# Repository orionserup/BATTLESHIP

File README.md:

# BATTLESHIP
A small battleship game built on a custom PCB using cheap chinese parts

Runs using a series of Shift registers running a custom game library, game library is based
on the popular shift register library

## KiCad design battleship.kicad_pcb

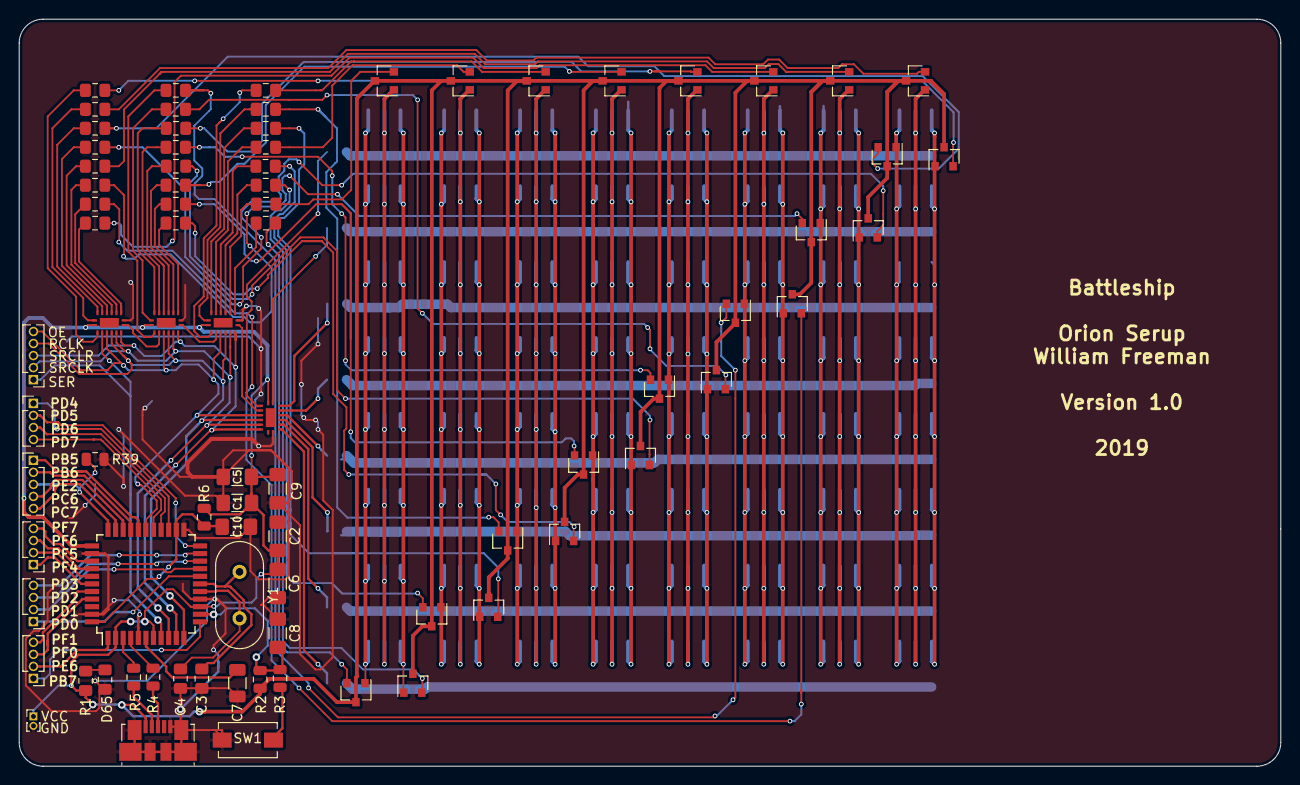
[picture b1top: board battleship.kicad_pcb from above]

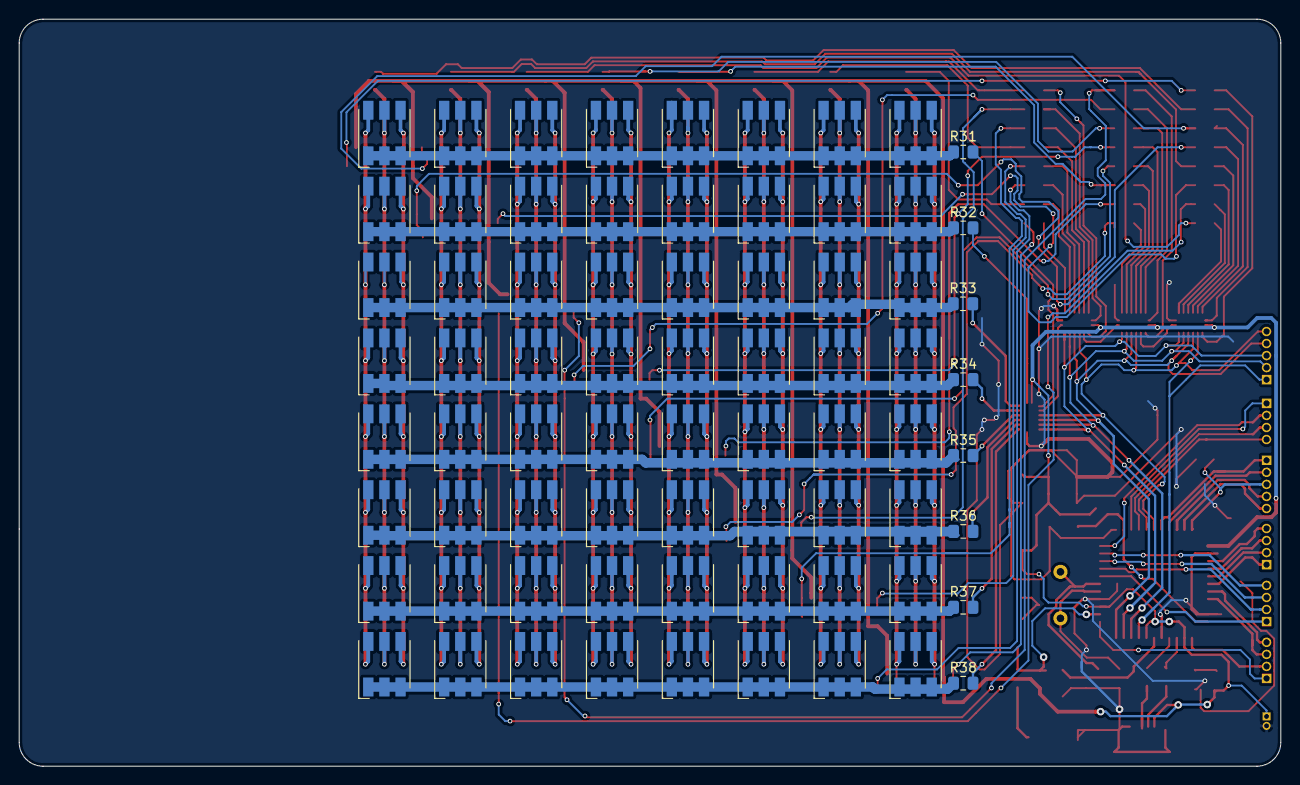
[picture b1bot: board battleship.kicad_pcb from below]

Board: 2 copper layers, 133.0 x 78.8 mm, 153 parts (72 on the bottom side), 130 nets.

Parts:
C1, C2, C5, C6, C9: 10UF; R_1206_3216Metric_Pad1.42x1.75mm_HandSolder
C3, C4: 22pf; C_0805_2012Metric_Pad1.15x1.40mm_HandSolder
C7: 1uF; R_1206_3216Metric
C8: 100nf; C_1206_3216Metric_Pad1.42x1.75mm_HandSolder
C10: 10uF; R_1206_3216Metric_Pad1.42x1.75mm_HandSolder
D1, D2, D3, D4, D5, D6, D7, D8, D9, D10, D11, D12, D13, D14, D15, D16, D17, D18, D19, D20, D21, D22, D23, D24, D25, D26, D27, D28, D29, D30, D31, D32, D33, D34, D35, D36, D37, D38, D39, D40, D41, D42, D43, D44, D45, D46, D47, D48, D49, D50, D51, D52, D53, D54, D55, D56, D57, D58, D59, D60, D61, D62, D63, D64: ASMT-YTC2-0AA02; LED_RGB_5050-6
D65: LED; R_0805_2012Metric_Pad1.15x1.40mm_HandSolder
J1: USB_B_Micro; USB_Micro-B_Molex_47346-0001
J2, J3, J4, J7: Conn_01x04; PinHeader_1x04_P1.27mm_Vertical
J5, J6: Conn_01x05; PinHeader_1x05_P1.27mm_Vertical
J8: Conn_01x02; PinHeader_1x02_P1.00mm_Vertical
Q1, Q2, Q3, Q4, Q5, Q6, Q7, Q8, Q9, Q10, Q11, Q12, Q13, Q14, Q15, Q16, Q17, Q18, Q19, Q20, Q21, Q22, Q23, Q24: 2N2219; SOT-23
R1: 1k; R_0805_2012Metric_Pad1.15x1.40mm_HandSolder
R2: 4.7k; R_0805_2012Metric
R3: 330; R_0805_2012Metric
R4, R5: 22; R_0805_2012Metric
R6: 1M; R_0805_2012Metric
R7, R8, R9, R10, R11, R12, R13, R14, R15, R16, R17, R18, R19, R20, R21, R22, R23, R24, R25, R26, R27, R28, R29, R30: 4.7K; R_0805_2012Metric_Pad1.15x1.40mm_HandSolder
R31, R32, R33, R34, R35, R36, R37, R38: 1K; R_0805_2012Metric_Pad1.15x1.40mm_HandSolder
R39: 1k; R_0805_2012Metric
SW1: SW_DPST_x2; SW_SPST_EVQPE1
U1: ATmega32U4RC-AU; TQFP-44_10x10mm_P0.8mm
U2, U3, U4, U5: 74HC595; dvqfn
Y1: 16MHz; Crystal_HC18-U_Vertical

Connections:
1: D1.6, D2.6, D3.6, D4.6, D5.6, D6.6, D7.6, D8.6, Q1.1
2: D1.5, D2.5, D3.5, D4.5, D5.5, D6.5, D7.5, D8.5, Q3.1
3: D1.4, D2.4, D3.4, D4.4, D5.4, D6.4, D7.4, D8.4, Q5.1
4: D9.6, D10.6, D11.6, D12.6, D13.6, D14.6, D15.6, D16.6, Q7.1
5: D9.5, D10.5, D11.5, D12.5, D13.5, D14.5, D15.5, D16.5, Q9.1
6: D9.4, D10.4, D11.4, D12.4, D13.4, D14.4, D15.4, D16.4, Q11.1
7: D17.6, D18.6, D19.6, D20.6, D21.6, D22.6, D23.6, D24.6, Q13.1
8: D17.5, D18.5, D19.5, D20.5, D21.5, D22.5, D23.5, D24.5, Q15.1
9: D17.4, D18.4, D19.4, D20.4, D21.4, D22.4, D23.4, D24.4, Q17.1
10: D25.6, D26.6, D27.6, D28.6, D29.6, D30.6, D31.6, D32.6, Q19.1
11: D25.5, D26.5, D27.5, D28.5, D29.5, D30.5, D31.5, D32.5, Q21.1
12: D25.4, D26.4, D27.4, D28.4, D29.4, D30.4, D31.4, D32.4, Q23.1
13: D33.6, D34.6, D35.6, D36.6, D37.6, D38.6, D39.6, D40.6, Q2.1
14: D33.5, D34.5, D35.5, D36.5, D37.5, D38.5, D39.5, D40.5, Q4.1
15: D33.4, D34.4, D35.4, D36.4, D37.4, D38.4, D39.4, D40.4, Q6.1
16: D41.6, D42.6, D43.6, D44.6, D45.6, D46.6, D47.6, D48.6, Q8.1
17: D41.5, D42.5, D43.5, D44.5, D45.5, D46.5, D47.5, D48.5, Q10.1
18: D41.4, D42.4, D43.4, D44.4, D45.4, D46.4, D47.4, D48.4, Q12.1
19: D49.6, D50.6, D51.6, D52.6, D53.6, D54.6, D55.6, D56.6, Q14.1
20: D49.5, D50.5, D51.5, D52.5, D53.5, D54.5, D55.5, D56.5, Q16.1
21: D49.4, D50.4, D51.4, D52.4, D53.4, D54.4, D55.4, D56.4, Q18.1
22: D57.6, D58.6, D59.6, D60.6, D61.6, D62.6, D63.6, D64.6, Q20.1
23: D57.5, D58.5, D59.5, D60.5, D61.5, D62.5, D63.5, D64.5, Q22.1
24: D57.4, D58.4, D59.4, D60.4, D61.4, D62.4, D63.4, D64.4, Q24.1
25: D1.1, D1.2, D1.3, D9.1, D9.2, D9.3, D17.1, D17.2, D17.3, D25.1, D25.2, D25.3, D33.1, D33.2, D33.3, D41.1, D41.2, D41.3, D49.1, D49.2, D49.3, D57.1, D57.2, D57.3, R31.1
26: D2.1, D2.2, D2.3, D10.1, D10.2, D10.3, D18.1, D18.2, D18.3, D26.1, D26.2, D26.3, D34.1, D34.2, D34.3, D42.1, D42.2, D42.3, D50.1, D50.2, D50.3, D58.1, D58.2, D58.3, R32.1
27: D3.1, D3.2, D3.3, D11.1, D11.2, D11.3, D19.1, D19.2, D19.3, D27.1, D27.2, D27.3, D35.1, D35.2, D35.3, D43.1, D43.2, D43.3, D51.1, D51.2, D51.3, D59.1, D59.2, D59.3, R33.1
28: D4.1, D4.2, D4.3, D12.1, D12.2, D12.3, D20.1, D20.2, D20.3, D28.1, D28.2, D28.3, D36.1, D36.2, D36.3, D44.1, D44.2, D44.3, D52.1, D52.2, D52.3, D60.1, D60.2, D60.3, R34.1
29: D5.1, D5.2, D5.3, D13.1, D13.2, D13.3, D21.1, D21.2, D21.3, D29.1, D29.2, D29.3, D37.1, D37.2, D37.3, D45.1, D45.2, D45.3, D53.1, D53.2, D53.3, D61.1, D61.2, D61.3, R35.1
30: D6.1, D6.2, D6.3, D14.1, D14.2, D14.3, D22.1, D22.2, D22.3, D30.1, D30.2, D30.3, D38.1, D38.2, D38.3, D46.1, D46.2, D46.3, D54.1, D54.2, D54.3, D62.1, D62.2, D62.3, R36.1
31: D7.1, D7.2, D7.3, D15.1, D15.2, D15.3, D23.1, D23.2, D23.3, D31.1, D31.2, D31.3, D39.1, D39.2, D39.3, D47.1, D47.2, D47.3, D55.1, D55.2, D55.3, D63.1, D63.2, D63.3, R37.1
32: D8.1, D8.2, D8.3, D16.1, D16.2, D16.3, D24.1, D24.2, D24.3, D32.1, D32.2, D32.3, D40.1, D40.2, D40.3, D48.1, D48.2, D48.3, D56.1, D56.2, D56.3, D64.1, D64.2, D64.3, R38.1
/PB5: J6.1, U1.29
/RESET: C8.2, R2.2, R3.1, U1.13
/SER: J5.1, U1.8, U2.14
/pb6: J6.2, U1.30
/pb7: J7.1, U1.12
/pc6: J6.4, U1.31
/pc7: J6.5, U1.32
/pd0: J2.1, U1.18
/pd1: J2.2, U1.19
/pd2: J2.3, U1.20
/pd3: J2.4, U1.21
/pd4: J3.1, U1.25
/pd5: J3.2, U1.22
/pd6: J3.3, U1.26
/pd7: J3.4, U1.27
/pe6: J7.2, U1.1
/pf0: J7.3, U1.41
/pf1: J7.4, U1.40
/pf4: J4.1, U1.39
/pf5: J4.2, U1.38
/pf6: J4.3, U1.37
/pf7: J4.4, U1.36
A1: Q1.2, R7.1
A2: Q3.2, R8.1
A3: Q5.2, R9.1
A4: Q7.2, R10.1
A5: Q9.2, R11.1
A6: Q11.2, R12.1
A7: Q13.2, R13.1
A8: Q15.2, R14.1
A9: Q17.2, R15.1
A10: Q19.2, R16.1
A11: Q21.2, R17.1
A12: Q23.2, R18.1
A13: Q2.2, R19.1
A14: Q4.2, R20.1
A15: Q6.2, R21.1
A16: Q8.2, R22.1
A17: Q10.2, R23.1
A18: Q12.2, R24.1
A19: Q14.2, R25.1
A20: Q16.2, R26.1
A21: Q18.2, R27.1
A22: Q20.2, R28.1
A23: Q22.2, R29.1
A24: Q24.2, R30.1
GND: C1.1, C2.1, C3.2, C4.2, C5.1, C6.1, C7.2, C8.1, C9.1, C10.1, D65.1, J1.5, J1.6, J8.2, R39.2, SW1.1, U1.5, U1.15, U1.23, U1.35, U1.43, U2.8, U3.8, U4.8, U5.8
unnamed: C3.1, U1.17, Y1.1
unnamed: C4.1, U1.16, Y1.2
unnamed: C7.1, U1.6
unnamed: C10.2, R6.1, U1.24, U1.44
unnamed: D65.2, R1.2
unnamed: J1.2, R5.1
unnamed: J1.3, R4.1
unnamed: R3.2, SW1.2
unnamed: R4.2, U1.4
unnamed: R5.2, U1.3
unnamed: R7.2, U2.15
unnamed: R8.2, U2.1
unnamed: R9.2, U2.2
unnamed: R10.2, U2.3
unnamed: R11.2, U2.4
unnamed: R12.2, U2.5
unnamed: R13.2, U2.6
unnamed: R14.2, U2.7
unnamed: R15.2, U3.15
unnamed: R16.2, U3.1
unnamed: R17.2, U3.2
unnamed: R18.2, U3.3
unnamed: R19.2, U3.4
unnamed: R20.2, U3.5
unnamed: R21.2, U3.6
unnamed: R22.2, U3.7
unnamed: R23.2, U4.15
unnamed: R24.2, U4.1
unnamed: R25.2, U4.2
unnamed: R26.2, U4.3
unnamed: R27.2, U4.4
unnamed: R28.2, U4.5
unnamed: R29.2, U4.6
unnamed: R30.2, U4.7
unnamed: R31.2, U5.15
unnamed: R32.2, U5.1
unnamed: R33.2, U5.2
unnamed: R34.2, U5.3
unnamed: R35.2, U5.4
unnamed: R36.2, U5.5
unnamed: R37.2, U5.6
unnamed: R38.2, U5.7
unnamed: U2.9, U3.14
unnamed: U3.9, U4.14
unnamed: U4.9, U5.14
OE: J5.5, U1.28, U2.13, U3.13, U4.13, U5.13
RCLK: J5.4, U1.11, U2.12, U3.12, U4.12, U5.12
SRCLK: J5.2, U1.9, U2.11, U3.11, U4.11, U5.11
SRCLR: J5.3, U1.10, U2.10, U3.10, U4.10, U5.10
VCC: C1.2, C2.2, C5.2, C6.2, C9.2, J1.1, J8.1, Q1.3, Q2.3, Q3.3, Q4.3, Q5.3, Q6.3, Q7.3, Q8.3, Q9.3, Q10.3, Q11.3, Q12.3, Q13.3, Q14.3, Q15.3, Q16.3, Q17.3, Q18.3, Q19.3, Q20.3, Q21.3, Q22.3, Q23.3, Q24.3, R1.1, R2.1, R6.2, U1.2, U1.7, U1.14, U1.34, U2.16, U3.16, U4.16, U5.16
pe2: J6.3, R39.1, U1.33

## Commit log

2019-10-20 schematic
2019-10-20 board
2019-10-20 gerber files
